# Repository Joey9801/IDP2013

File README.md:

IDP2013
=======

IDP2013 group M203, software and electrical

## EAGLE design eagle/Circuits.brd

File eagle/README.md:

These schematics and Layouts were produced in EagleCAD 6.5.0

Joe Roberts 2013

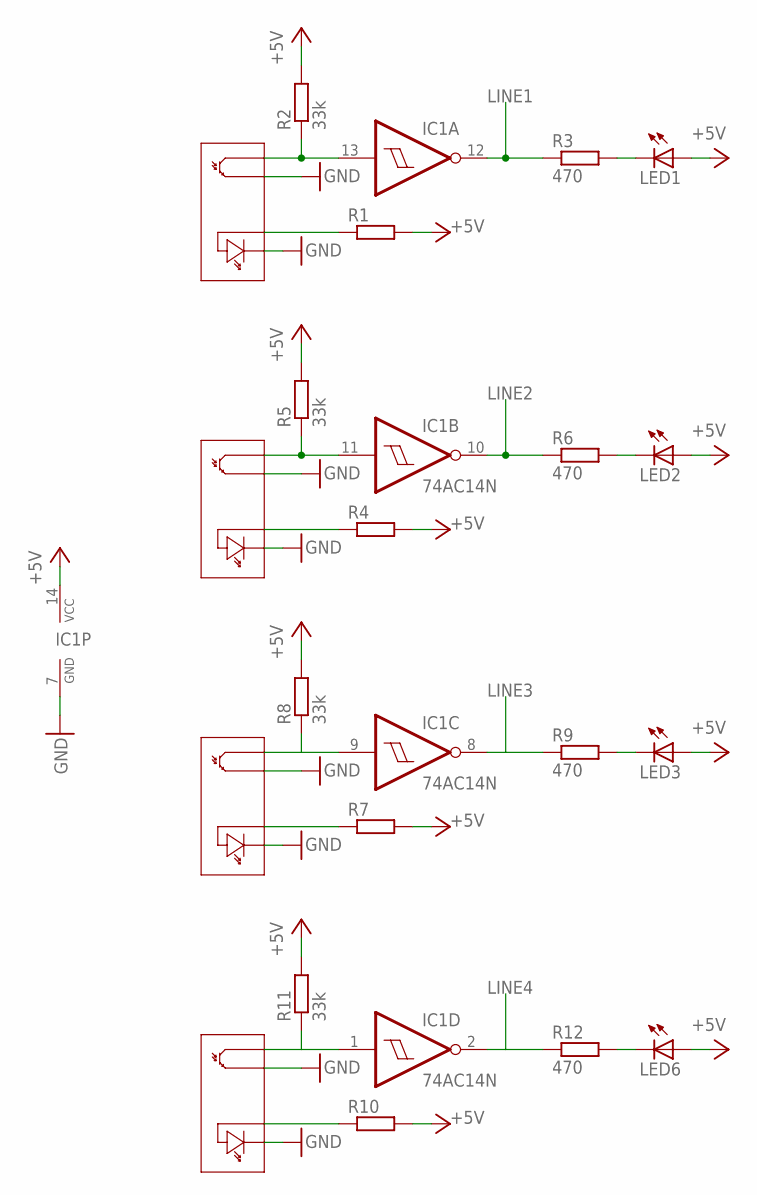
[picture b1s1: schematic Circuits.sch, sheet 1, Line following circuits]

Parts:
IC1: 74AC14N; DIL14
LED1, LED2, LED3, LED6: TLLR4400; LED3MM
R1, R4, R7, R10: R-EU_0207/7; 0207/7
R2, R5, R8, R11: 33k; 0207/7
R3, R6, R9, R12: 470; 0207/7

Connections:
+5V: IC1.14 (VCC), LED1.A, LED2.A, LED3.A, LED6.A, R1.2, R2.2, R4.2, R5.2, R7.2, R8.2, R10.2, R11.2; also elsewhere on the board
GND: IC1.7 (GND); also elsewhere on the board
LINE1: IC1.12 (O), R3.1; also elsewhere on the board
LINE2: IC1.10 (O), R6.1; also elsewhere on the board
LINE3: IC1.8 (O), R9.1; also elsewhere on the board
LINE4: IC1.2 (O), R12.1; also elsewhere on the board
unnamed: IC1.13 (I), R2.1
unnamed: LED1.K (C), R3.2
unnamed: IC1.11 (I), R5.1
unnamed: LED2.K (C), R6.2
unnamed: IC1.9 (I), R8.1
unnamed: LED3.K (C), R9.2
unnamed: IC1.1 (I), R11.1
unnamed: LED6.K (C), R12.2

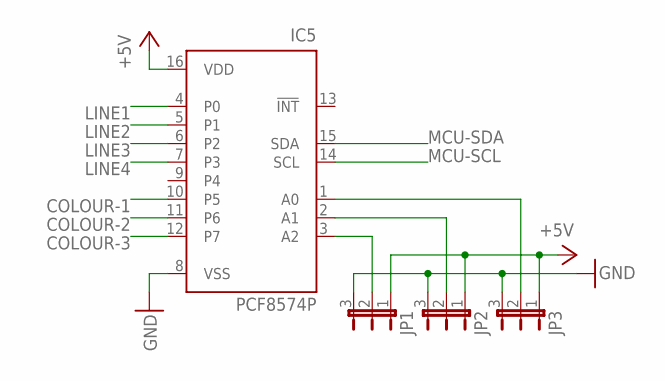
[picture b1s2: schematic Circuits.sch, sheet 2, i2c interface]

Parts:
IC5: PCF8574P; DIL16
JP1, JP2, JP3: JP2W

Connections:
+5V: IC5.16 (VDD), JP1.1, JP2.1, JP3.1; also elsewhere on the board
COLOUR-1: IC5.10 (P5); also elsewhere on the board
COLOUR-2: IC5.11 (P6); also elsewhere on the board
COLOUR-3: IC5.12 (P7); also elsewhere on the board
GND: IC5.8 (VSS), JP1.3, JP2.3, JP3.3; also elsewhere on the board
LINE1: IC5.4 (P0); also elsewhere on the board
LINE2: IC5.5 (P1); also elsewhere on the board
LINE3: IC5.6 (P2); also elsewhere on the board
LINE4: IC5.7 (P3); also elsewhere on the board
MCU-SCL: IC5.14 (SCL)
MCU-SDA: IC5.15 (SDA)
unnamed: IC5.3 (A2), JP1.2
unnamed: IC5.2 (A1), JP2.2
unnamed: IC5.1 (A0), JP3.2

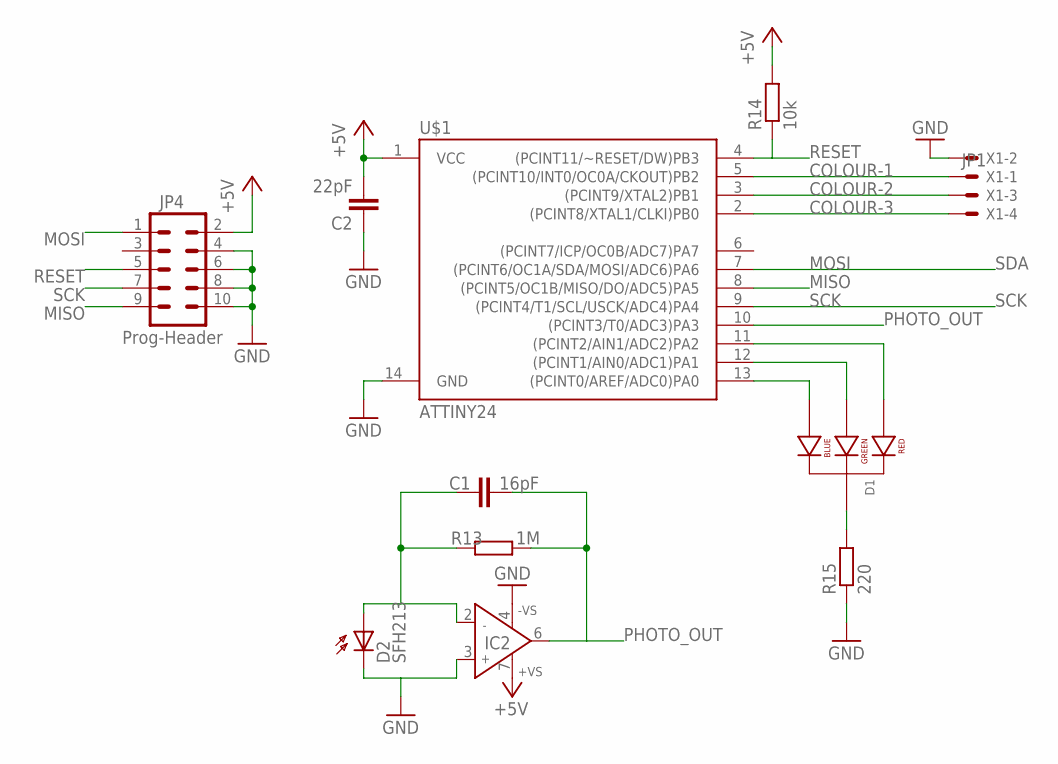
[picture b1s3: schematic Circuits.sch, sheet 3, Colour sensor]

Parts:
C1: 16pF; C025-024X044
C2: 22pF; C025-024X044
D1: LED-RGB-CC-THRUCLEAR; LED-RGB-THRU
D2: SFH213; SFH205
IC2: mcp603; DIL08
JP4: Prog-Header; 2X5-SHROUDED
R13: 1M; 0204/5
R14: 10k; 0207/7
R15: 220; 0207/7
U$1: ATTINY24; DIL14
X1: JP1; 22-23-2041

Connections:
+5V: C2.2, IC2.7 (+VS), JP4.2, R14.2, U$1.1 (VCC); also elsewhere on the board
COLOUR-1: U$1.5 ((PCINT10/INT0/OC0A/CKOUT)PB2), X1.1; also elsewhere on the board
COLOUR-2: U$1.3 ((PCINT9/XTAL2)PB1), X1.3; also elsewhere on the board
COLOUR-3: U$1.2 ((PCINT8/XTAL1/CLKI)PB0), X1.4; also elsewhere on the board
GND: C2.1, D2.K (C), IC2.3 (IN+), IC2.4 (-VS), JP4.4, JP4.6, JP4.8, JP4.10, R15.1, U$1.14 (GND), X1.2; also elsewhere on the board
MISO: JP4.9, U$1.8 ((PCINT5/OC1B/MISO/DO/ADC5)PA5)
MOSI: JP4.1, U$1.7 ((PCINT6/OC1A/SDA/MOSI/ADC6)PA6)
unnamed: D1.4 (BLUE_CATHODE), U$1.13 ((PCINT0/AREF/ADC0)PA0)
unnamed: D1.3 (GREEN_CATHODE), U$1.12 ((PCINT1/AIN0/ADC1)PA1)
unnamed: D1.1 (RED_CATHODE), U$1.11 ((PCINT2/AIN1/ADC2)PA2)
unnamed: C1.1, D2.A, IC2.2 (IN-), R13.1
unnamed: D1.2 (CATHODE), R15.2
PHOTO_OUT: C1.2, IC2.6 (OUT), R13.2, U$1.10 ((PCINT3/T0/ADC3)PA3); also elsewhere on the board
RESET: JP4.5, R14.1, U$1.4 ((PCINT11/~RESET/DW)PB3)
SCK: JP4.7, U$1.9 ((PCINT4/T1/SCL/USCK/ADC4)PA4)

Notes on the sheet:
SDA
SCK

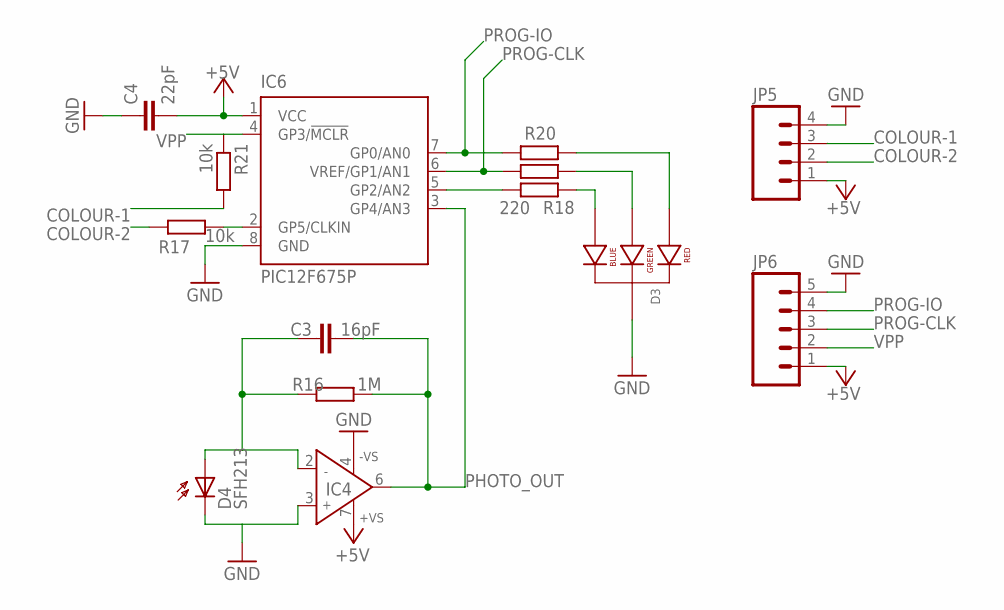
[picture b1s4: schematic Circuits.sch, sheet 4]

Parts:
C3: 16pF; C025-024X044
C4: 22pF; C025-024X044
D3: LED-RGB-CC-THRUCLEAR; LED-RGB-THRU
D4: SFH213; SFH205
IC4: mcp603; DIL08
IC6: PIC12F675P; DIL8
JP5: M04LONGPADS; 1X04_LONGPADS
JP6: M05PTH_LONGPADS; 1X05_LONGPADS
R16: 1M; 0204/5
R17, R21: 10k; 0207/7
R18, R19, R20: 220; 0207/7

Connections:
+5V: C4.2, IC4.7 (+VS), IC6.1 (VCC), JP5.1, JP6.1; also elsewhere on the board
COLOUR-1: JP5.3, R21.2; also elsewhere on the board
COLOUR-2: JP5.2, R17.1; also elsewhere on the board
GND: C4.1, D3.2 (CATHODE), D4.K (C), IC4.3 (IN+), IC4.4 (-VS), IC6.8 (GND), JP5.4, JP6.5; also elsewhere on the board
unnamed: D3.4 (BLUE_CATHODE), R18.1
unnamed: D3.3 (GREEN_CATHODE), R19.1
unnamed: IC6.2 (GP5/CLKIN), R17.2
unnamed: C3.1, D4.A, IC4.2 (IN-), R16.1
unnamed: D3.1 (RED_CATHODE), R20.1
unnamed: IC6.5 (GP2/AN2), R18.2
PHOTO_OUT: C3.2, IC4.6 (OUT), IC6.3 (GP4/AN3), R16.2; also elsewhere on the board
PROG-CLK: IC6.6 (VREF/GP1/AN1), JP6.3, R19.2
PROG-IO: IC6.7 (GP0/AN0), JP6.4, R20.2
VPP: IC6.4 (GP3/!MCLR), JP6.2, R21.1

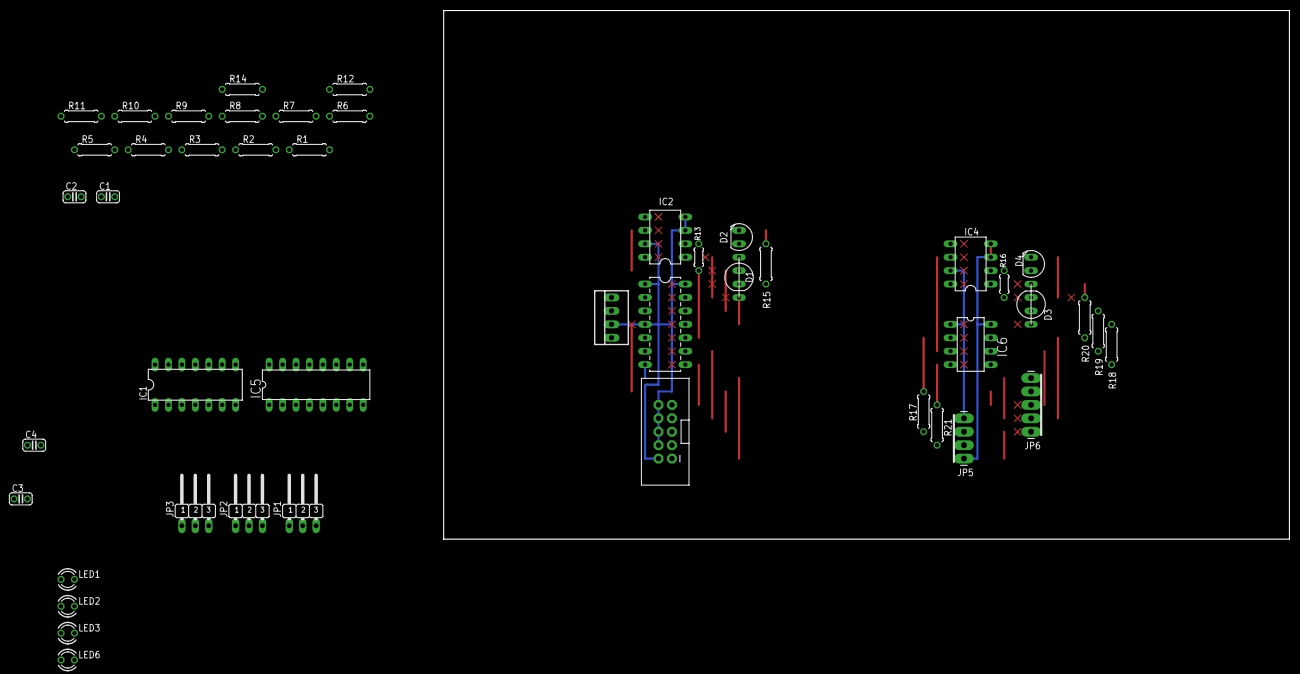
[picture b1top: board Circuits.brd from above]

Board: 2 copper layers, 160.0 x 100.0 mm, 77 parts (0 on the bottom side), 39 nets.

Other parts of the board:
U$2, U$3, U$4, U$5, U$6, U$7, U$8, U$9, U$10, U$11, U$12, U$13, U$14, U$15, U$16, U$17, U$18, U$19, U$20, U$21, U$22, U$23, U$24, U$25, U$26, U$27, U$28, U$29, U$30, U$31, U$32: BREAK

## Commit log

2013-11-12 Colour sensor schematic
2013-11-12 Tidy up
2013-11-12 colour sensor code outlined
2013-11-12 silly typo
2013-11-12 line sensor + merged circuits
2013-11-12 a lot of the colour code - compiles
2013-11-18 everything's dandy with electronics
2013-11-18 Fixed .gitignore
2013-11-18 eagle readme
2013-11-18 robot libraries
2013-11-18 week 1 code
2013-11-18 main source template
2013-11-18 main template
2013-11-18 fixed makefiles for use outside cued
2013-11-18 formatted week1 exercises
2013-11-19 design acceptance examples
2013-11-20 Added PIC colour sensor as DA Backup
2013-11-20 Proposed macro-structure
2013-11-20 connection initialises
2013-11-21 Line following with error handling
2013-11-22 formatted last commit with astyle
2013-11-22 line following in separate file
2013-11-22 indicator test and turning outline
2013-11-22 Rewrote line following to make concise, functionality preserved
2013-11-23 debug functions and navigation template
2013-11-25 corners - tested and working
2013-11-25 removed compiled code accidentally included
2013-11-26 turning tidied up and low level functions moved to io.cpp
2013-11-26 Removed accidentally included file
2013-11-26 route following function written
2013-11-27 idp_MAP
2013-11-27 Route following logic working
2013-11-27 slightly better debug messages
2013-11-28 working line following and demos
2013-11-28 Line following & Demos on fast motors(40rpm)
2013-11-28 Collection route for fast motors
2013-11-28 Improved debug messages
2013-11-28 Begun implementing proper error handling
2013-11-28 set_indicators() configured correctly
2013-11-28 silly error with switch statement
2013-11-28 Added optional final turn
2013-11-28 set_intent() prototype
2013-11-28 outlined plan_route()
2013-11-28 added new idp_error for plan_route()
2013-11-28 plan_route() template
2013-11-29 set_motors accepts negative values, global ROT_SPEED defined
2013-11-29 error checking routes
2013-11-29 modified lots of bits, makes far fewer errors
2013-11-29 Full working competition logic
2013-12-01 removed accidentally included temp file
2013-12-02 Function to rejoin line after action
2013-12-02 colour sensor reading function
2013-12-02 Implemented a virtual flag for testing w/o robot
2013-12-03 Added blank detection and tweaked
2013-12-03 Working competition run (w/ random parcel placeholder)
2013-12-03 Navigation reverses to line at belt/sleigh
2013-12-03 Hopefully formatting better
2013-12-03 Follow to junction after reverse turn
2013-12-04 complete with silly reversing things - all working
2013-12-05 fine tuning
2013-12-05 Added colour sensor panic option, readied code for comp
2013-12-05 Added test_collection(void) for last minute panicking
2013-12-06 goes home at the end
2013-12-06 forgot break; statements, broke everything (fixed now)

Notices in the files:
parts and their libraries:
SparkFun-DigitalIC: Licensing: CC v3.0 Share-Alike You are welcome to use this library for commercial purposes.
